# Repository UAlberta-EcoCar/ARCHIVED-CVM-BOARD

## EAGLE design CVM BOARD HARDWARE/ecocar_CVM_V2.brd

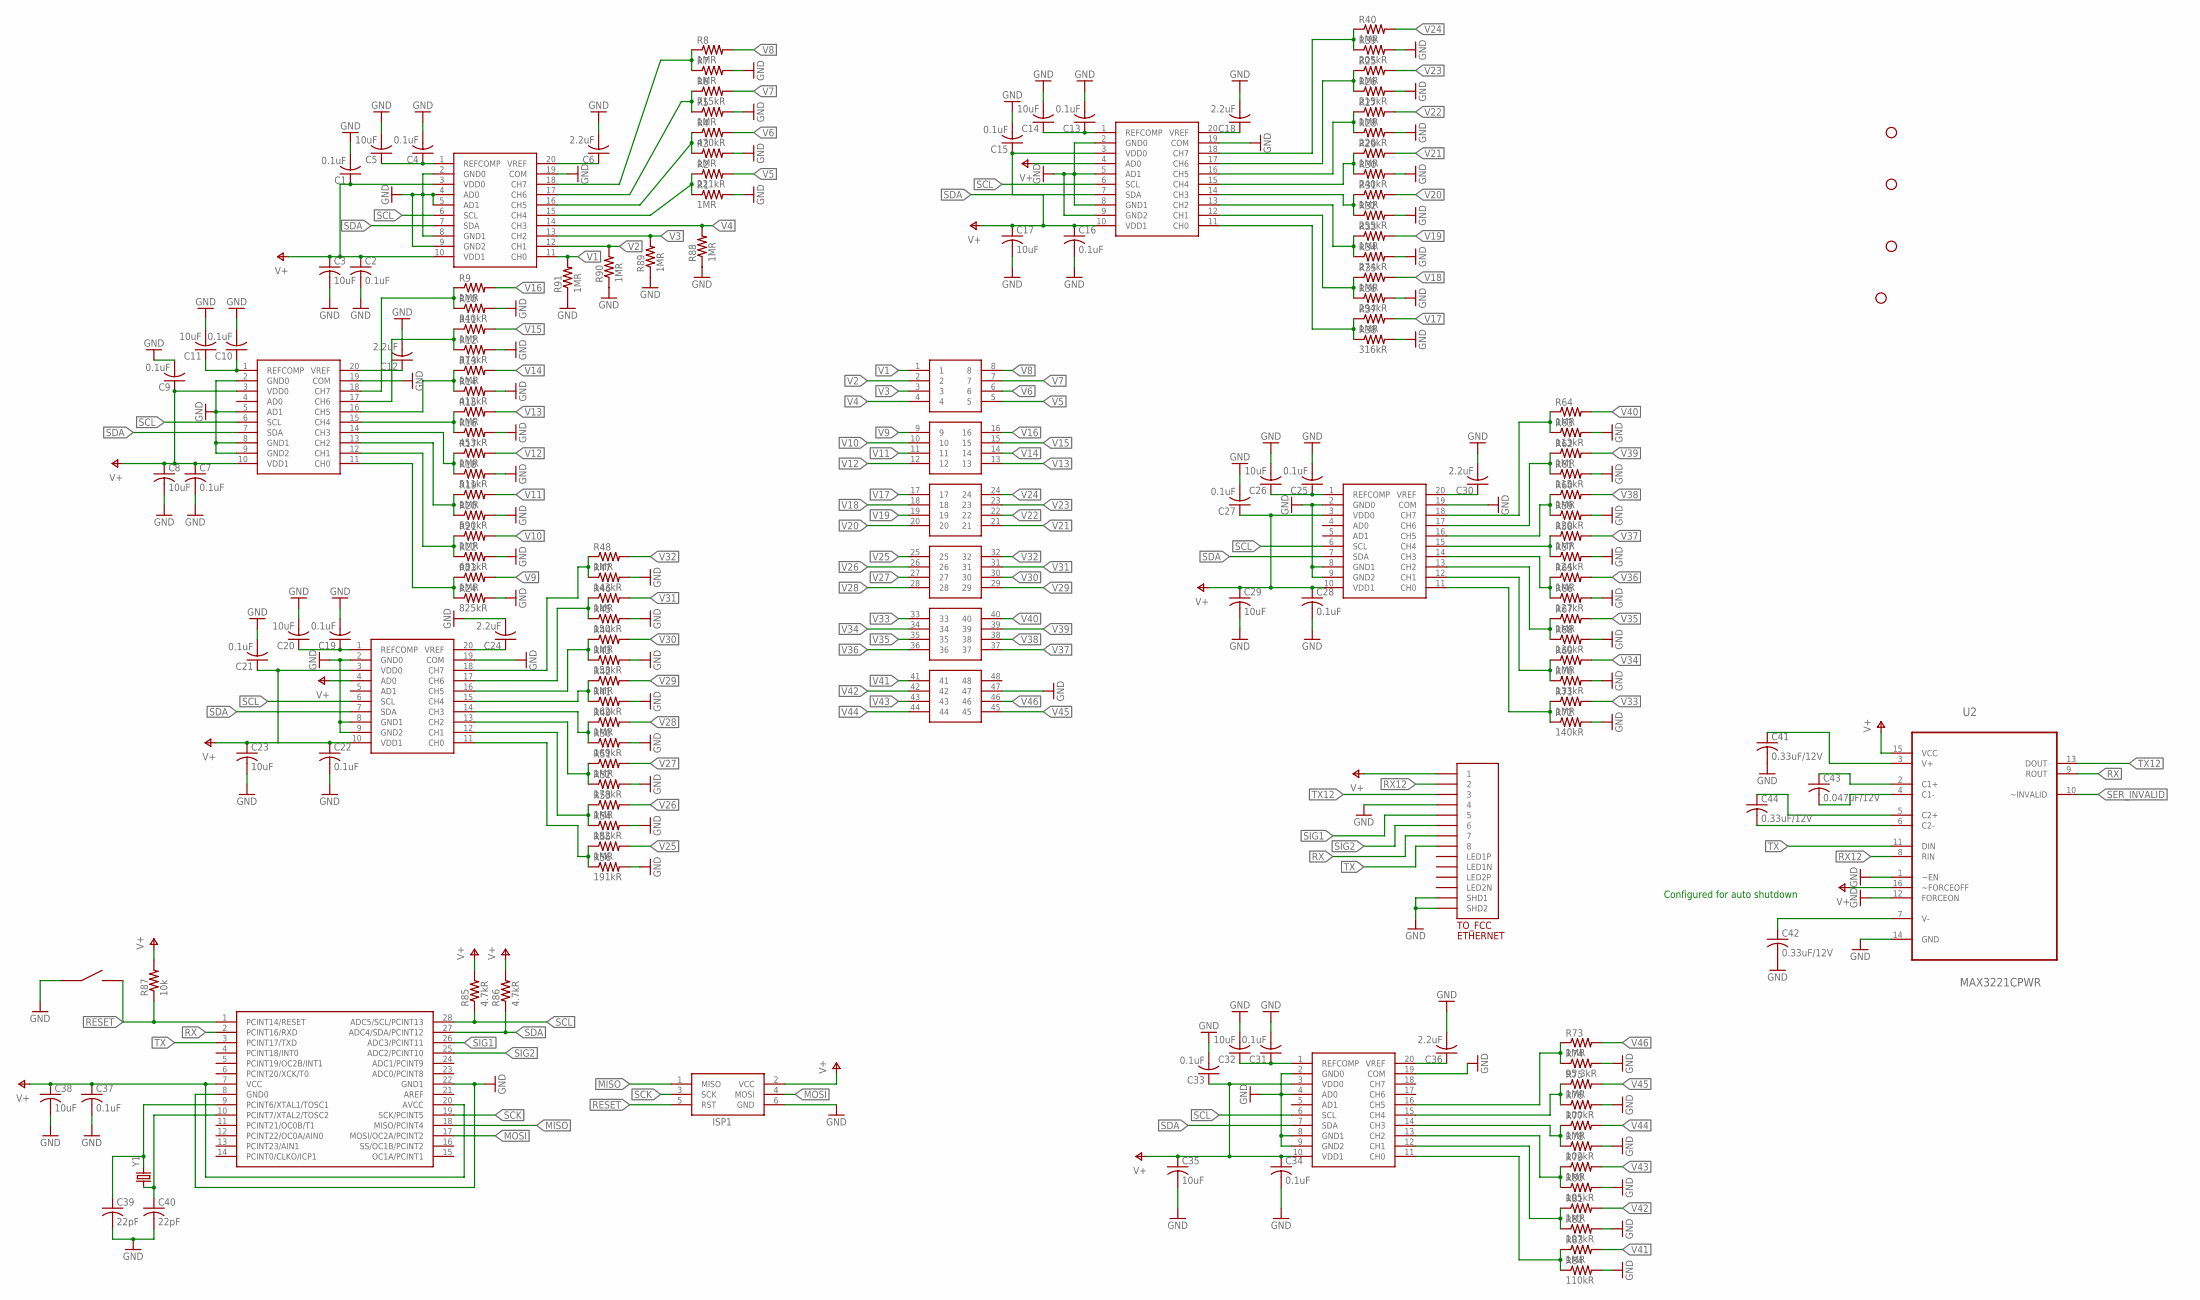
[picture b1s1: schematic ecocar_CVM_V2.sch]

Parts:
0001000, 0001001, 0001010, 0001011, 0011000, 0011001: LTC2309; TSSOP20
C1, C2, C4, C7, C9, C10, C13, C15, C16, C19, C21, C22, C25, C27, C28, C31, C33, C34, C37: 0.1uF; C0805
C3, C5, C8, C11, C14, C17, C20, C23, C26, C29, C32, C35, C38: 10uF; C0805
C6, C12, C18, C24, C30, C36: 2.2uF; C0805
C39, C40: 22pF; C0805
C41, C42, C44: 0.33uF/12V; C0805
C43: 0.047uF/12V; C0805
ISP1: AVRISP-BOX
R1, R3, R5, R7, R8, R9, R11, R13, R15, R17, R19, R21, R23, R25, R27, R29, R31, R33, R35, R37, R40, R42, R44, R46, R48, R49, R51, R53, R55, R58, R60, R62, R64, R65, R67, R69, R71, R73, R75, R77, R79, R81, R83, R88, R89, R90, R91: 1MR; R0805
R2: 221kR; R0805
R4: 470kR; R0805
R6: 715kR; R0805
R10: 340kR; R0805
R12: 374kR; R0805
R14: 412kR; R0805
R16: 453kR; R0805
R18: 511kR; R0805
R20: 590kR; R0805
R22: 681kR; R0805
R24: 825kR; R0805
R26: 215kR; R0805
R28: 226kR; R0805
R30: 240kR; R0805
R32: 255kR; R0805
R34: 274kR; R0805
R36: 294kR; R0805
R38: 316kR; R0805
R39: 205kR; R0805
R41: 162kR; R0805
R43: 158kR; R0805
R45: 150kR; R0805
R47: 143kR; R0805
R50: 169kR; R0805
R52: 178kR; R0805
R54: 182kR; R0805
R56: 191kR; R0805
R57: 124kR; R0805
R59: 120kR; R0805
R61: 115kR; R0805
R63: 113kR; R0805
R66: 127kR; R0805
R68: 130kR; R0805
R70: 133kR; R0805
R72: 140kR; R0805
R74: 95.3kR; R0805
R76: 100kR; R0805
R78: 102kR; R0805
R80: 105kR; R0805
R82: 107kR; R0805
R84: 110kR; R0805
R85, R86: 4.7kR; R0805
R87: 10k; R0805
RESET_BTN: EG4621CT-ND
STANDOFF1, STANDOFF2, STANDOFF3, STANDOFF4: STAND-OFF
TO_FCC: ETHERNET; A122645-ND
U2: MAX3221CPWR; SOP65P640X120-16N
U$1: ATMEGA328P; DIL28-3
U$3: 6-RJ45; 48-PIN-THROUGHHOLE
Y1: CRYSTALHC49US; HC49US

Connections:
GND: 0001000.2 (GND0), 0001000.4 (AD0), 0001000.5 (AD1), 0001000.8 (GND1), 0001000.9 (GND2), 0001000.19 (COM), 0001001.2 (GND0), 0001001.5 (AD1), 0001001.8 (GND1), 0001001.9 (GND2), 0001001.19 (COM), 0001010.2 (GND0), 0001010.5 (AD1), 0001010.8 (GND1), 0001010.9 (GND2), 0001010.19 (COM), 0001011.2 (GND0), 0001011.8 (GND1), 0001011.9 (GND2), 0001011.19 (COM), 0011000.2 (GND0), 0011000.8 (GND1), 0011000.9 (GND2), 0011000.19 (COM), 0011001.2 (GND0), 0011001.4 (AD0), 0011001.8 (GND1), 0011001.9 (GND2), 0011001.19 (COM), C1.2, C2.2, C3.2, C4.2, C5.2, C6.2, C7.2, C8.2, C9.2, C10.2, C11.2, C12.2, C13.2, C14.2, C15.2, C16.2, C17.2, C18.2, C19.2, C20.2, C21.2, C22.2, C23.2, C24.2, C25.2, C26.2, C27.2, C28.2, C29.2, C30.2, C31.2, C32.2, C33.2, C34.2, C35.2, C36.2, C37.2, C38.2, C39.2, C40.2, C41.2, C42.2, ISP1.6 (GND), R1.2, R3.2, R5.2, R7.2, R10.2, R12.2, R14.2, R16.2, R18.2, R20.2, R22.2, R24.2, R26.2, R28.2, R30.2, R32.2, R34.2, R36.2, R38.2, R39.2, R41.2, R43.2, R45.2, R47.2, R50.2, R52.2, R54.2, R56.2, R57.2, R59.2, R61.2, R63.2, R66.2, R68.2, R70.2, R72.2, R74.2, R76.2, R78.2, R80.2, R82.2, R84.2, R88.1, R89.1, R90.1, R91.1, RESET_BTN.P$1, RESET_BTN.P$2, TO_FCC.P$4 (4), TO_FCC.P$13 (SHD1), TO_FCC.P$14 (SHD2), U2.1 (~EN), U2.12 (FORCEON), U2.14 (GND), U$1.8 (GND0), U$1.22 (GND1), U$3.47
MISO: ISP1.1 (MISO), U$1.18 (MISO/PCINT4)
MOSI: ISP1.4 (MOSI), U$1.17 (MOSI/OC2A/PCINT2)
unnamed: 0001000.1 (REFCOMP), C4.1, C5.1
unnamed: 0001000.20 (VREF), C6.1
unnamed: 0001001.11 (CH0), R23.1, R24.1
unnamed: 0001001.1 (REFCOMP), C10.1, C11.1
unnamed: 0001001.20 (VREF), C12.1
unnamed: 0001001.12 (CH1), R21.1, R22.1
unnamed: 0001000.15 (CH4), R1.1, R2.1
unnamed: 0001000.16 (CH5), R3.1, R4.1
unnamed: 0001000.17 (CH6), R5.1, R6.1
unnamed: 0001000.18 (CH7), R7.1, R8.1
unnamed: 0001001.13 (CH2), R19.1, R20.1
unnamed: 0001001.14 (CH3), R17.1, R18.1
unnamed: 0001001.15 (CH4), R15.1, R16.1
unnamed: 0001001.16 (CH5), R13.1, R14.1
unnamed: 0001001.17 (CH6), R11.1, R12.1
unnamed: 0001001.18 (CH7), R9.1, R10.1
unnamed: 0001010.1 (REFCOMP), C13.1, C14.1
unnamed: 0011000.1 (REFCOMP), C25.1, C26.1
unnamed: 0001010.11 (CH0), R37.1, R38.1
unnamed: 0001010.20 (VREF), C18.1
unnamed: 0001010.12 (CH1), R35.1, R36.1
unnamed: 0001010.13 (CH2), R33.1, R34.1
unnamed: 0001010.14 (CH3), R31.1, R32.1
unnamed: 0001010.15 (CH4), R29.1, R30.1
unnamed: 0001010.16 (CH5), R27.1, R28.1
unnamed: 0001010.17 (CH6), R25.1, R26.1
unnamed: 0001010.18 (CH7), R39.1, R40.1
unnamed: 0001011.1 (REFCOMP), C19.1, C20.1
unnamed: 0011001.1 (REFCOMP), C31.1, C32.1
unnamed: 0011001.20 (VREF), C36.1
unnamed: 0001011.20 (VREF), C24.1
unnamed: 0001011.11 (CH0), R55.1, R56.1
unnamed: 0001011.12 (CH1), R53.1, R54.1
unnamed: 0001011.13 (CH2), R51.1, R52.1
unnamed: 0001011.14 (CH3), R49.1, R50.1
unnamed: 0001011.15 (CH4), R41.1, R42.1
unnamed: 0001011.16 (CH5), R43.1, R44.1
unnamed: 0001011.17 (CH6), R45.1, R46.1
unnamed: 0001011.18 (CH7), R47.1, R48.1
unnamed: 0011000.20 (VREF), C30.1
unnamed: 0011000.11 (CH0), R71.1, R72.1
unnamed: 0011000.12 (CH1), R69.1, R70.1
unnamed: 0011000.13 (CH2), R67.1, R68.1
unnamed: 0011000.14 (CH3), R65.1, R66.1
unnamed: 0011000.15 (CH4), R57.1, R58.1
unnamed: 0011000.16 (CH5), R59.1, R60.1
unnamed: 0011000.17 (CH6), R61.1, R62.1
unnamed: 0011000.18 (CH7), R63.1, R64.1
unnamed: C39.1, U$1.9 (PCINT6/XTAL1/TOSC1), Y1.2
unnamed: C40.1, U$1.10 (PCINT7/XTAL2/TOSC2), Y1.1
unnamed: 0011001.11 (CH0), R83.1, R84.1
unnamed: 0011001.12 (CH1), R81.1, R82.1
unnamed: 0011001.13 (CH2), R79.1, R80.1
unnamed: 0011001.14 (CH3), R77.1, R78.1
unnamed: 0011001.15 (CH4), R75.1, R76.1
unnamed: 0011001.16 (CH5), R73.1, R74.1
unnamed: C41.1, U2.3 (V+)
unnamed: C43.1, U2.2 (C1+)
unnamed: C43.2, U2.4 (C1-)
unnamed: C44.1, U2.5 (C2+)
unnamed: C44.2, U2.6 (C2-)
unnamed: C42.1, U2.7 (V-)
RESET: ISP1.5 (RST), R87.1, RESET_BTN.P$3, RESET_BTN.P$4, U$1.1 (PCINT14/RESET)
RX: TO_FCC.P$7 (7), U2.9 (ROUT), U$1.2 (PCINT16/RXD)
RX12: TO_FCC.P$2 (2), U2.8 (RIN)
SCK: ISP1.3 (SCK), U$1.19 (SCK/PCINT5)
SCL: 0001000.6 (SCL), 0001001.6 (SCL), 0001010.6 (SCL), 0001011.6 (SCL), 0011000.6 (SCL), 0011001.6 (SCL), R85.1, U$1.28 (ADC5/SCL/PCINT13)
SDA: 0001000.7 (SDA), 0001001.7 (SDA), 0001010.7 (SDA), 0001011.7 (SDA), 0011000.7 (SDA), 0011001.7 (SDA), R86.1, U$1.27 (ADC4/SDA/PCINT12)
SER_INVALID: U2.10 (~INVALID)
SIG1: TO_FCC.P$5 (5), U$1.26 (ADC3/PCINT11)
SIG2: TO_FCC.P$6 (6), U$1.25 (ADC2/PCINT10)
TX: TO_FCC.P$8 (8), U2.11 (DIN), U$1.3 (PCINT17/TXD)
TX12: TO_FCC.P$3 (3), U2.13 (DOUT)
V1: 0001000.11 (CH0), R91.2, U$3.1
V2: 0001000.12 (CH1), R90.2, U$3.2
V3: 0001000.13 (CH2), R89.2, U$3.3
V4: 0001000.14 (CH3), R88.2, U$3.4
V5: R2.2, U$3.5
V6: R4.2, U$3.6
V7: R6.2, U$3.7
V8: R8.2, U$3.8
V9: R23.2, U$3.9
V10: R21.2, U$3.10
V11: R19.2, U$3.11
V12: R17.2, U$3.12
V13: R15.2, U$3.13
V14: R13.2, U$3.14
V15: R11.2, U$3.15
V16: R9.2, U$3.16
V17: R37.2, U$3.17
V18: R35.2, U$3.18
V19: R33.2, U$3.19
V20: R31.2, U$3.20
V21: R29.2, U$3.21
V22: R27.2, U$3.22
V23: R25.2, U$3.23
V24: R40.2, U$3.24
V25: R55.2, U$3.25
V26: R53.2, U$3.26
V27: R51.2, U$3.27
V28: R49.2, U$3.28
V29: R42.2, U$3.29
V30: R44.2, U$3.30
V31: R46.2, U$3.31
V32: R48.2, U$3.32
V33: R71.2, U$3.33
V34: R69.2, U$3.34
V35: R67.2, U$3.35
V36: R65.2, U$3.36
V37: R58.2, U$3.37
V38: R60.2, U$3.38
V39: R62.2, U$3.39
V40: R64.2, U$3.40
V41: R83.2, U$3.41
V42: R81.2, U$3.42
V43: R79.2, U$3.43
V44: R77.2, U$3.44
V45: R75.2, U$3.45
V46: R73.2, U$3.46
V+: 0001000.3 (VDD0), 0001000.10 (VDD1), 0001001.3 (VDD0), 0001001.10 (VDD1), 0001010.3 (VDD0), 0001010.4 (AD0), 0001010.10 (VDD1), 0001011.3 (VDD0), 0001011.4 (AD0), 0001011.10 (VDD1), 0011000.3 (VDD0), 0011000.10 (VDD1), 0011001.3 (VDD0), 0011001.10 (VDD1), C1.1, C2.1, C3.1, C7.1, C8.1, C9.1, C15.1, C16.1, C17.1, C21.1, C22.1, C23.1, C27.1, C28.1, C29.1, C33.1, C34.1, C35.1, C37.1, C38.1, ISP1.2 (VCC), R85.2, R86.2, R87.2, TO_FCC.P$1 (1), U2.15 (VCC), U2.16 (~FORCEOFF), U$1.7 (VCC), U$1.20 (AVCC)

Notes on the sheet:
Configured for auto shutdown

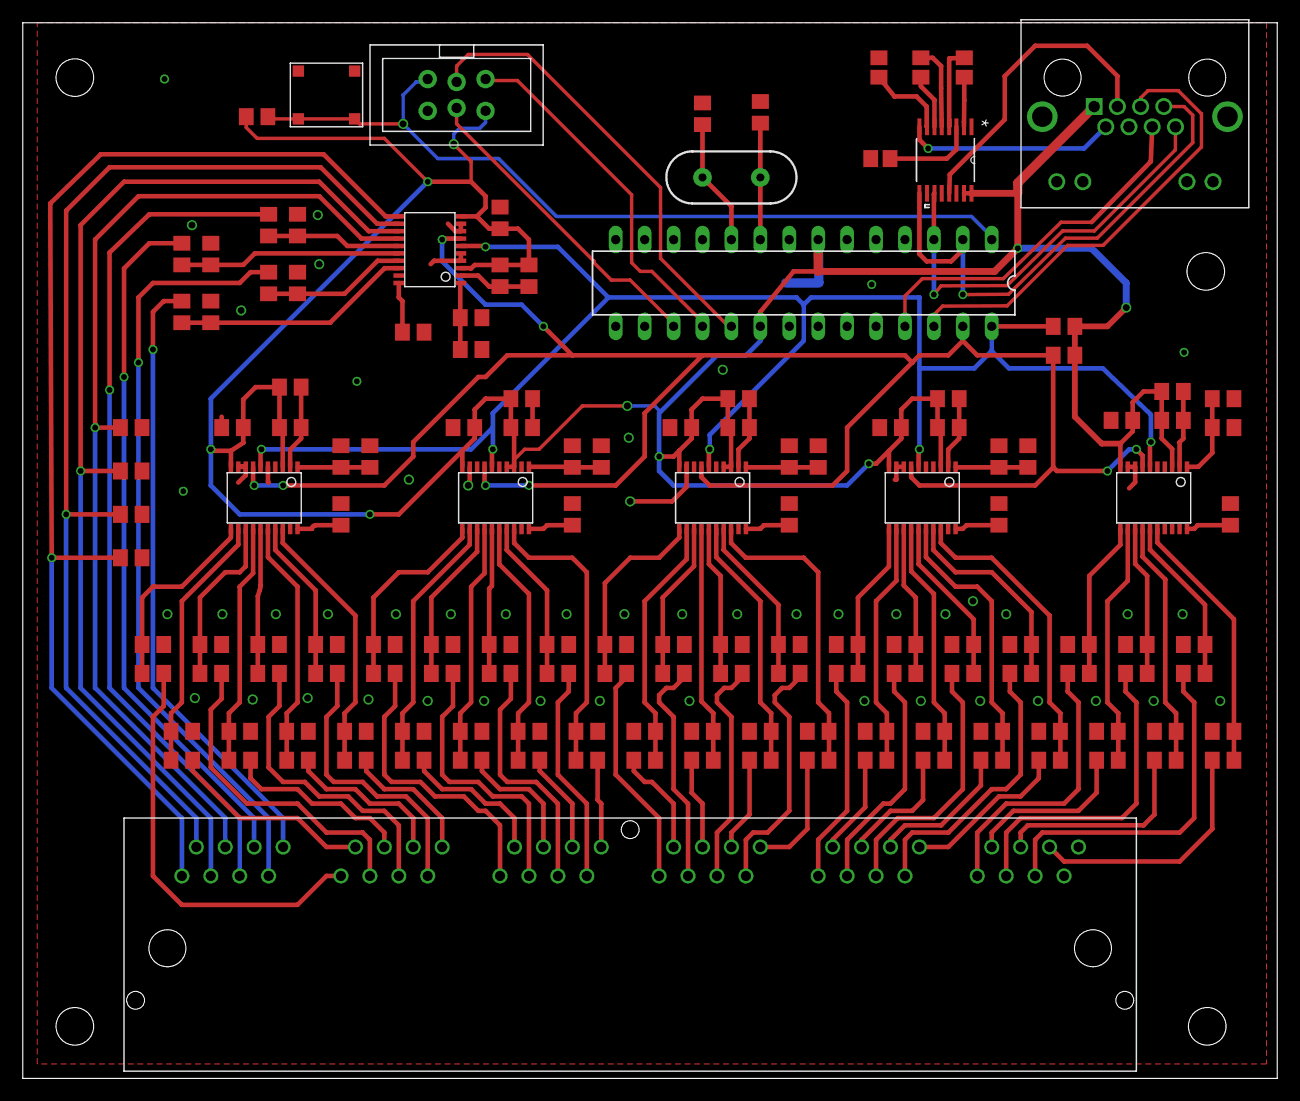
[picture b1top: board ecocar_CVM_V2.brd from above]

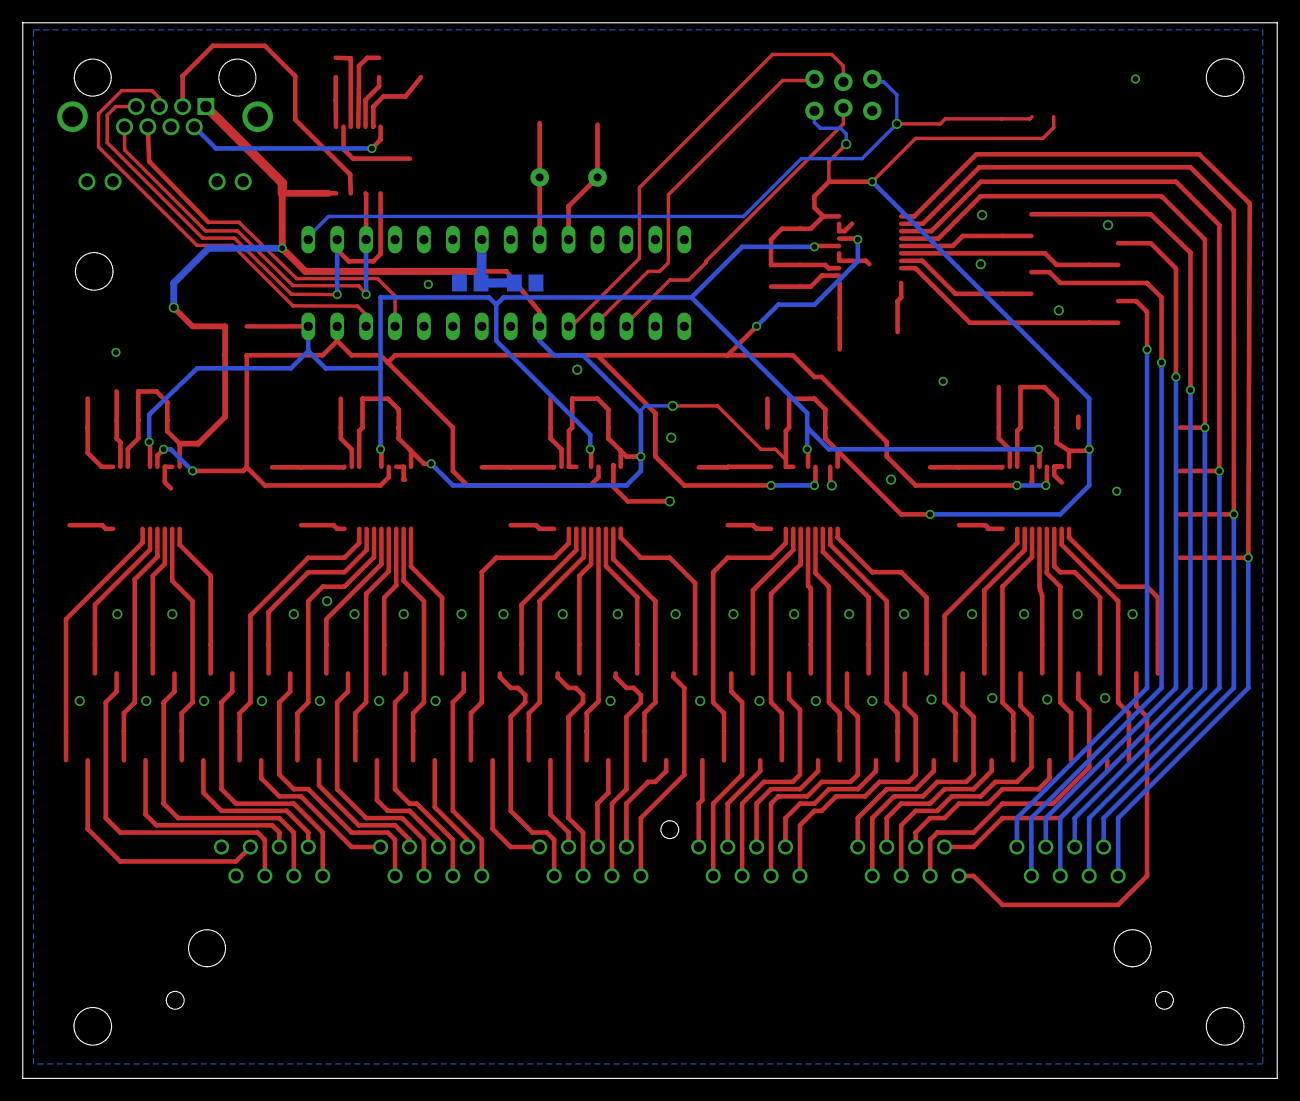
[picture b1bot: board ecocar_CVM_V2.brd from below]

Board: 2 copper layers, 110.2 x 92.7 mm, 152 parts (2 on the bottom side), 122 nets.

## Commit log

2019-09-02 adding some code
2019-09-09 Cleaning up, simplifying and adding watch dog timer to code

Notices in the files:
parts and their libraries:
SparkFun-FreqCtrl: Licensing: Creative Commons ShareAlike 4.0 International - https://creativecommons.org/licenses/by-sa/4.0
